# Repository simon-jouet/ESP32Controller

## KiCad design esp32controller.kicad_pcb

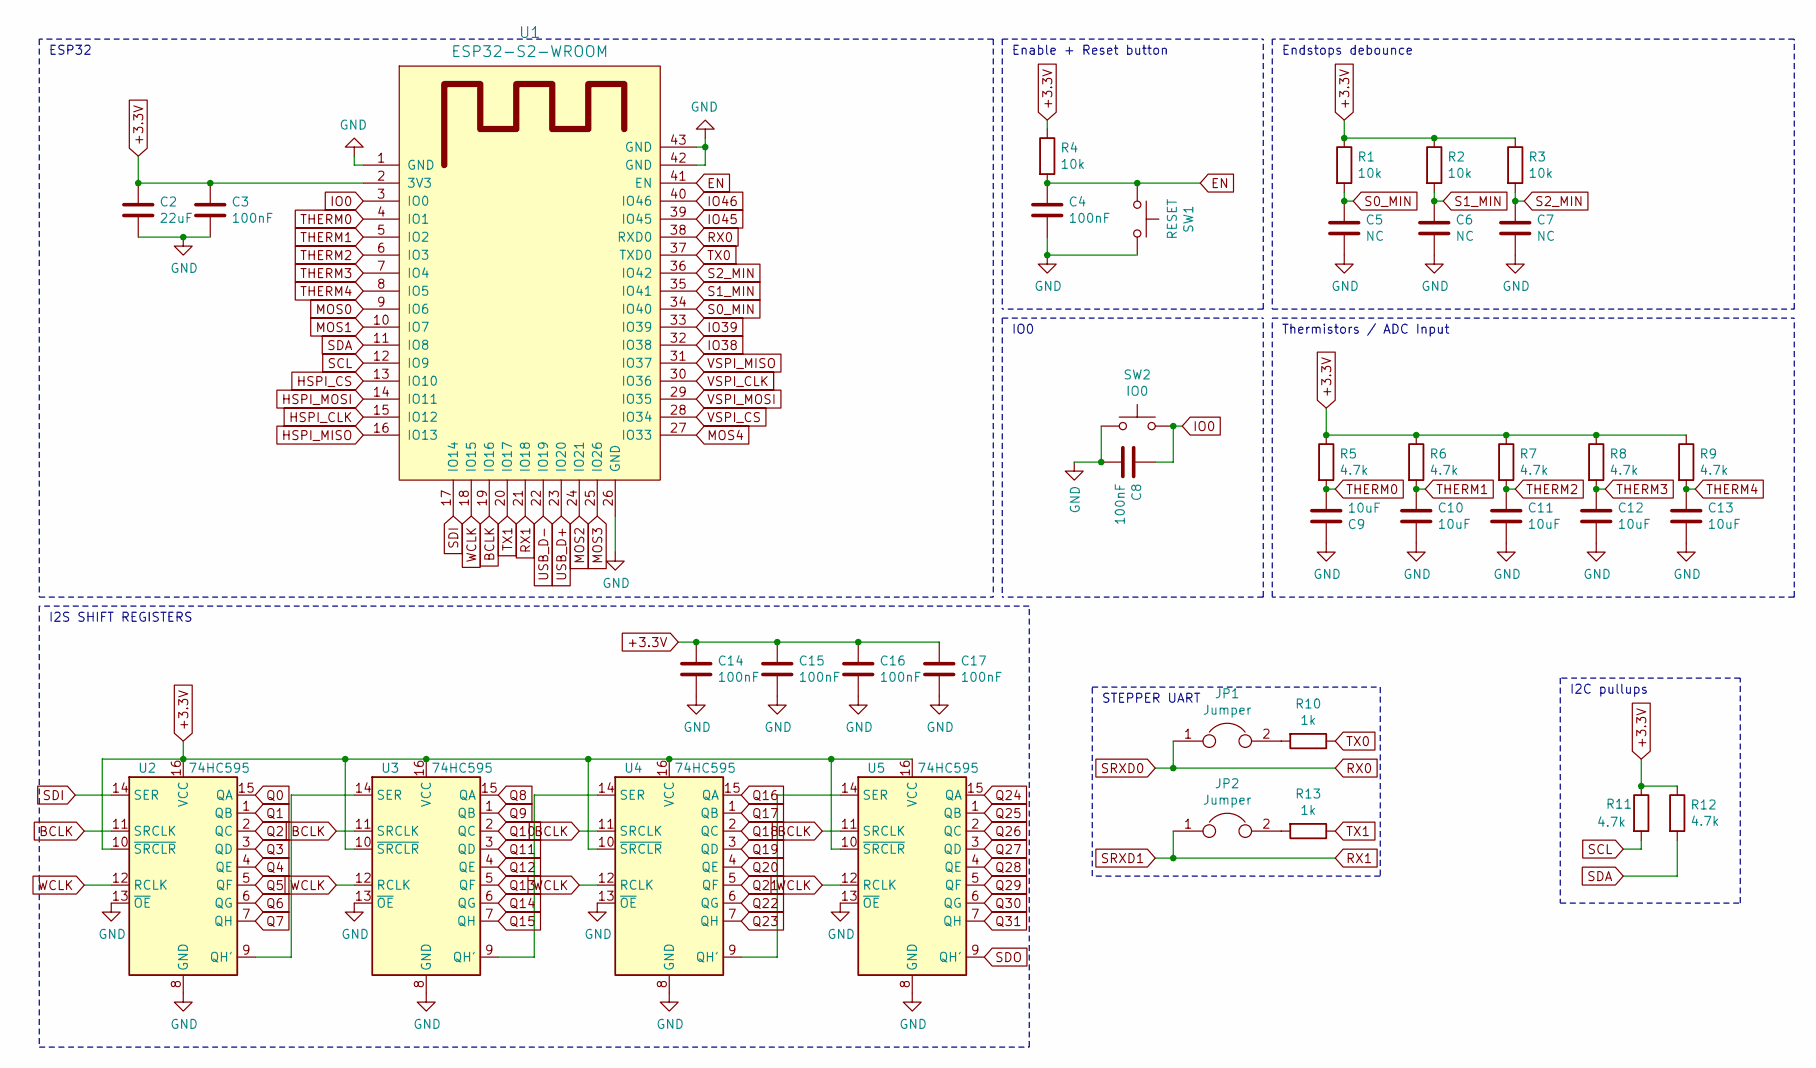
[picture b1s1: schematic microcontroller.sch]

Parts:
C2: 22uF; C_0805_2012Metric
C3, C4, C8, C14, C15, C16, C17: 100nF; C_0603_1608Metric
C5, C6, C7: NC; C_0603_1608Metric
C9, C10, C11, C12, C13: 10uF; C_0805_2012Metric
JP1, JP2: Jumper; PinHeader_1x02_P2.54mm_Vertical
R1, R2, R3, R4: 10k; R_0603_1608Metric
R5, R6, R7, R8, R9, R11, R12: 4.7k; R_0603_1608Metric
R10, R13: 1k; R_0603_1608Metric
SW1: RESET; SW_Push_1P1T_NO_6x6mm_H9.5mm
SW2: IO0; SW_Push_1P1T_NO_6x6mm_H9.5mm
U1: ESP32-S2-WROOM; esp32-s2-wrooom
U2, U3, U4, U5: 74HC595; TSSOP-16_4.4x5mm_P0.65mm

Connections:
+3.3V: C2.1, C3.1, C14.1, C15.1, C16.1, C17.1, R1.1, R2.1, R3.1, R4.1, R5.1, R6.1, R7.1, R8.1, R9.1, R11.1, R12.1, U1.2 (3V3), U2.10 (~SRCLR), U2.16 (VCC), U3.10 (~SRCLR), U3.16 (VCC), U4.10 (~SRCLR), U4.16 (VCC), U5.10 (~SRCLR), U5.16 (VCC); also elsewhere on the board
BCLK: U1.19 (IO16), U2.11 (SRCLK), U3.11 (SRCLK), U4.11 (SRCLK), U5.11 (SRCLK)
EN: C4.1, R4.2, SW1.1, U1.41 (EN); also elsewhere on the board
GND: C2.2, C3.2, C4.2, C5.2, C6.2, C7.2, C8.2, C9.1, C10.2, C11.2, C12.2, C13.2, C14.2, C15.2, C16.2, C17.2, SW1.2, SW2.1, U1.1 (GND), U1.26 (GND), U1.42 (GND), U1.43 (GND), U2.8 (GND), U2.13 (~OE), U3.8 (GND), U3.13 (~OE), U4.8 (GND), U4.13 (~OE), U5.8 (GND), U5.13 (~OE); also elsewhere on the board
HSPI_CLK: U1.15 (IO12); also elsewhere on the board
HSPI_CS: U1.13 (IO10); also elsewhere on the board
HSPI_MISO: U1.16 (IO13); also elsewhere on the board
HSPI_MOSI: U1.14 (IO11); also elsewhere on the board
IO0: C8.1, SW2.2, U1.3 (IO0); also elsewhere on the board
IO38: U1.32 (IO38); also elsewhere on the board
IO39: U1.33 (IO39); also elsewhere on the board
IO45: U1.39 (IO45); also elsewhere on the board
IO46: U1.40 (IO46); also elsewhere on the board
MOS0: U1.9 (IO6); also elsewhere on the board
MOS1: U1.10 (IO7); also elsewhere on the board
MOS2: U1.24 (IO21); also elsewhere on the board
MOS3: U1.25 (IO26); also elsewhere on the board
MOS4: U1.27 (IO33); also elsewhere on the board
unnamed: JP1.2, R10.2
unnamed: JP2.2, R13.2
unnamed: U2.9 (QH'), U3.14 (SER)
unnamed: U3.9 (QH'), U4.14 (SER)
unnamed: U4.9 (QH'), U5.14 (SER)
Q0: U2.15 (QA); also elsewhere on the board
Q1: U2.1 (QB); also elsewhere on the board
Q2: U2.2 (QC); also elsewhere on the board
Q3: U2.3 (QD); also elsewhere on the board
Q4: U2.4 (QE); also elsewhere on the board
Q5: U2.5 (QF); also elsewhere on the board
Q6: U2.6 (QG); also elsewhere on the board
Q7: U2.7 (QH); also elsewhere on the board
Q8: U3.15 (QA); also elsewhere on the board
Q9: U3.1 (QB); also elsewhere on the board
Q10: U3.2 (QC); also elsewhere on the board
Q11: U3.3 (QD); also elsewhere on the board
Q12: U3.4 (QE); also elsewhere on the board
Q13: U3.5 (QF); also elsewhere on the board
Q14: U3.6 (QG); also elsewhere on the board
Q15: U3.7 (QH); also elsewhere on the board
Q16: U4.15 (QA); also elsewhere on the board
Q17: U4.1 (QB); also elsewhere on the board
Q18: U4.2 (QC); also elsewhere on the board
Q19: U4.3 (QD); also elsewhere on the board
Q20: U4.4 (QE); also elsewhere on the board
Q21: U4.5 (QF); also elsewhere on the board
Q22: U4.6 (QG); also elsewhere on the board
Q23: U4.7 (QH); also elsewhere on the board
Q24: U5.15 (QA); also elsewhere on the board
Q25: U5.1 (QB); also elsewhere on the board
Q26: U5.2 (QC); also elsewhere on the board
Q27: U5.3 (QD); also elsewhere on the board
Q28: U5.4 (QE); also elsewhere on the board
Q29: U5.5 (QF); also elsewhere on the board
Q30: U5.6 (QG); also elsewhere on the board
Q31: U5.7 (QH); also elsewhere on the board
RX0: JP1.1, U1.38 (RXD0); also elsewhere on the board
RX1: JP2.1, U1.21 (IO18); also elsewhere on the board
S0_MIN: C5.1, R1.2, U1.34 (IO40); also elsewhere on the board
S1_MIN: C6.1, R2.2, U1.35 (IO41); also elsewhere on the board
S2_MIN: C7.1, R3.2, U1.36 (IO42); also elsewhere on the board
SCL: R11.2, U1.12 (IO9); also elsewhere on the board
SDA: R12.2, U1.11 (IO8); also elsewhere on the board
SDI: U1.17 (IO14), U2.14 (SER)
THERM0: C9.2, R5.2, U1.4 (IO1); also elsewhere on the board
THERM1: C10.1, R6.2, U1.5 (IO2); also elsewhere on the board
THERM2: C11.1, R7.2, U1.6 (IO3); also elsewhere on the board
THERM3: C12.1, R8.2, U1.7 (IO4); also elsewhere on the board
THERM4: C13.1, R9.2, U1.8 (IO5); also elsewhere on the board
TX0: R10.1, U1.37 (TXD0); also elsewhere on the board
TX1: R13.1, U1.20 (IO17); also elsewhere on the board
USB_D+: U1.23 (IO20); also elsewhere on the board
USB_D-: U1.22 (IO19); also elsewhere on the board
VSPI_CLK: U1.30 (IO36); also elsewhere on the board
VSPI_CS: U1.28 (IO34); also elsewhere on the board
VSPI_MISO: U1.31 (IO37); also elsewhere on the board
VSPI_MOSI: U1.29 (IO35); also elsewhere on the board
WCLK: U1.18 (IO15), U2.12 (RCLK), U3.12 (RCLK), U4.12 (RCLK), U5.12 (RCLK)

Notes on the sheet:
ESP32
I2S SHIFT REGISTERS
Endstops debounce
Enable + Reset button
Thermistors / ADC Input
I2C pullups
IO0
STEPPER UART

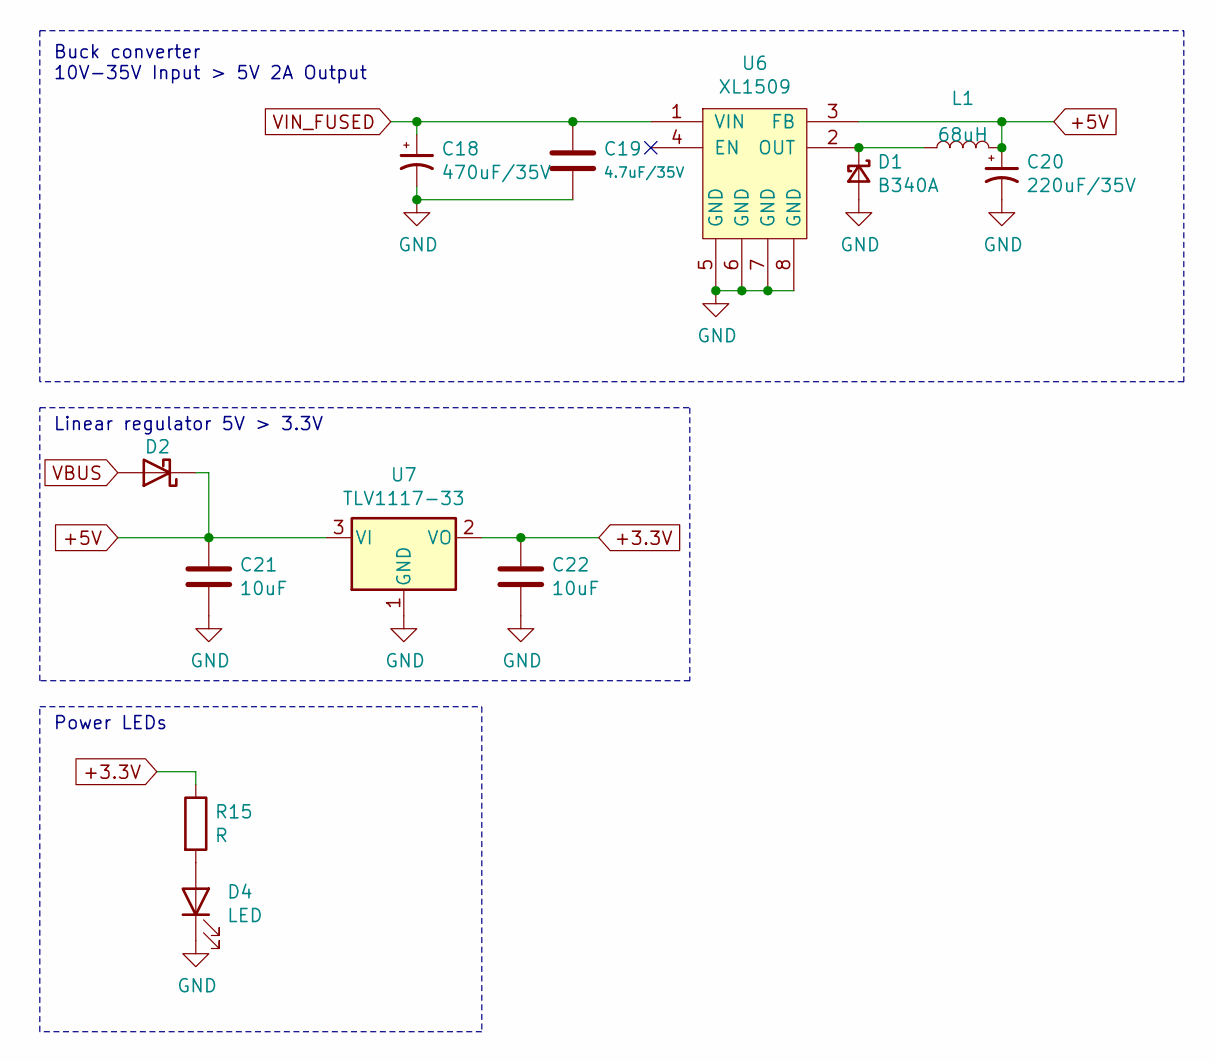
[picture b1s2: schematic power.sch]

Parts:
C18: 470uF/35V; CP_Elec_10x10
C19: 4.7uF/35V; C_0805_2012Metric
C20: 220uF/35V; C_1210_3225Metric
C21, C22: 10uF; C_0805_2012Metric
D1: B340A; D_SMA
D2: D_Schottky; D_SOD-323_HandSoldering
D4: LED; LED_0805_2012Metric
L1: 68uH; L_7.3x7.3_H3.5
R15: R; R_0603_1608Metric
U6: XL1509; SOIC-8_3.9x4.9mm_P1.27mm
U7: TLV1117-33; SOT-223-3_TabPin2

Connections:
+3.3V: C22.1, R15.1, U7.2 (VO); also elsewhere on the board
+5V: C20.1, C21.1, D2.1 (K), L1.2, U6.3 (FB), U7.3 (VI); also elsewhere on the board
GND: C18.2, C19.2, C20.2, C21.2, C22.2, D1.2 (A), D4.1 (K), U6.5 (GND), U6.6 (GND), U6.7 (GND), U6.8 (GND), U7.1 (GND); also elsewhere on the board
unnamed: D1.1 (K), L1.1, U6.2 (OUT)
unnamed: D4.2 (A), R15.2
VBUS: D2.2 (A); also elsewhere on the board
VIN_FUSED: C18.1, C19.1, U6.1 (VIN); also elsewhere on the board

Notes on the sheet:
Linear regulator 5V > 3.3V
Power LEDs
Buck converter 10V-35V Input > 5V 2A Output

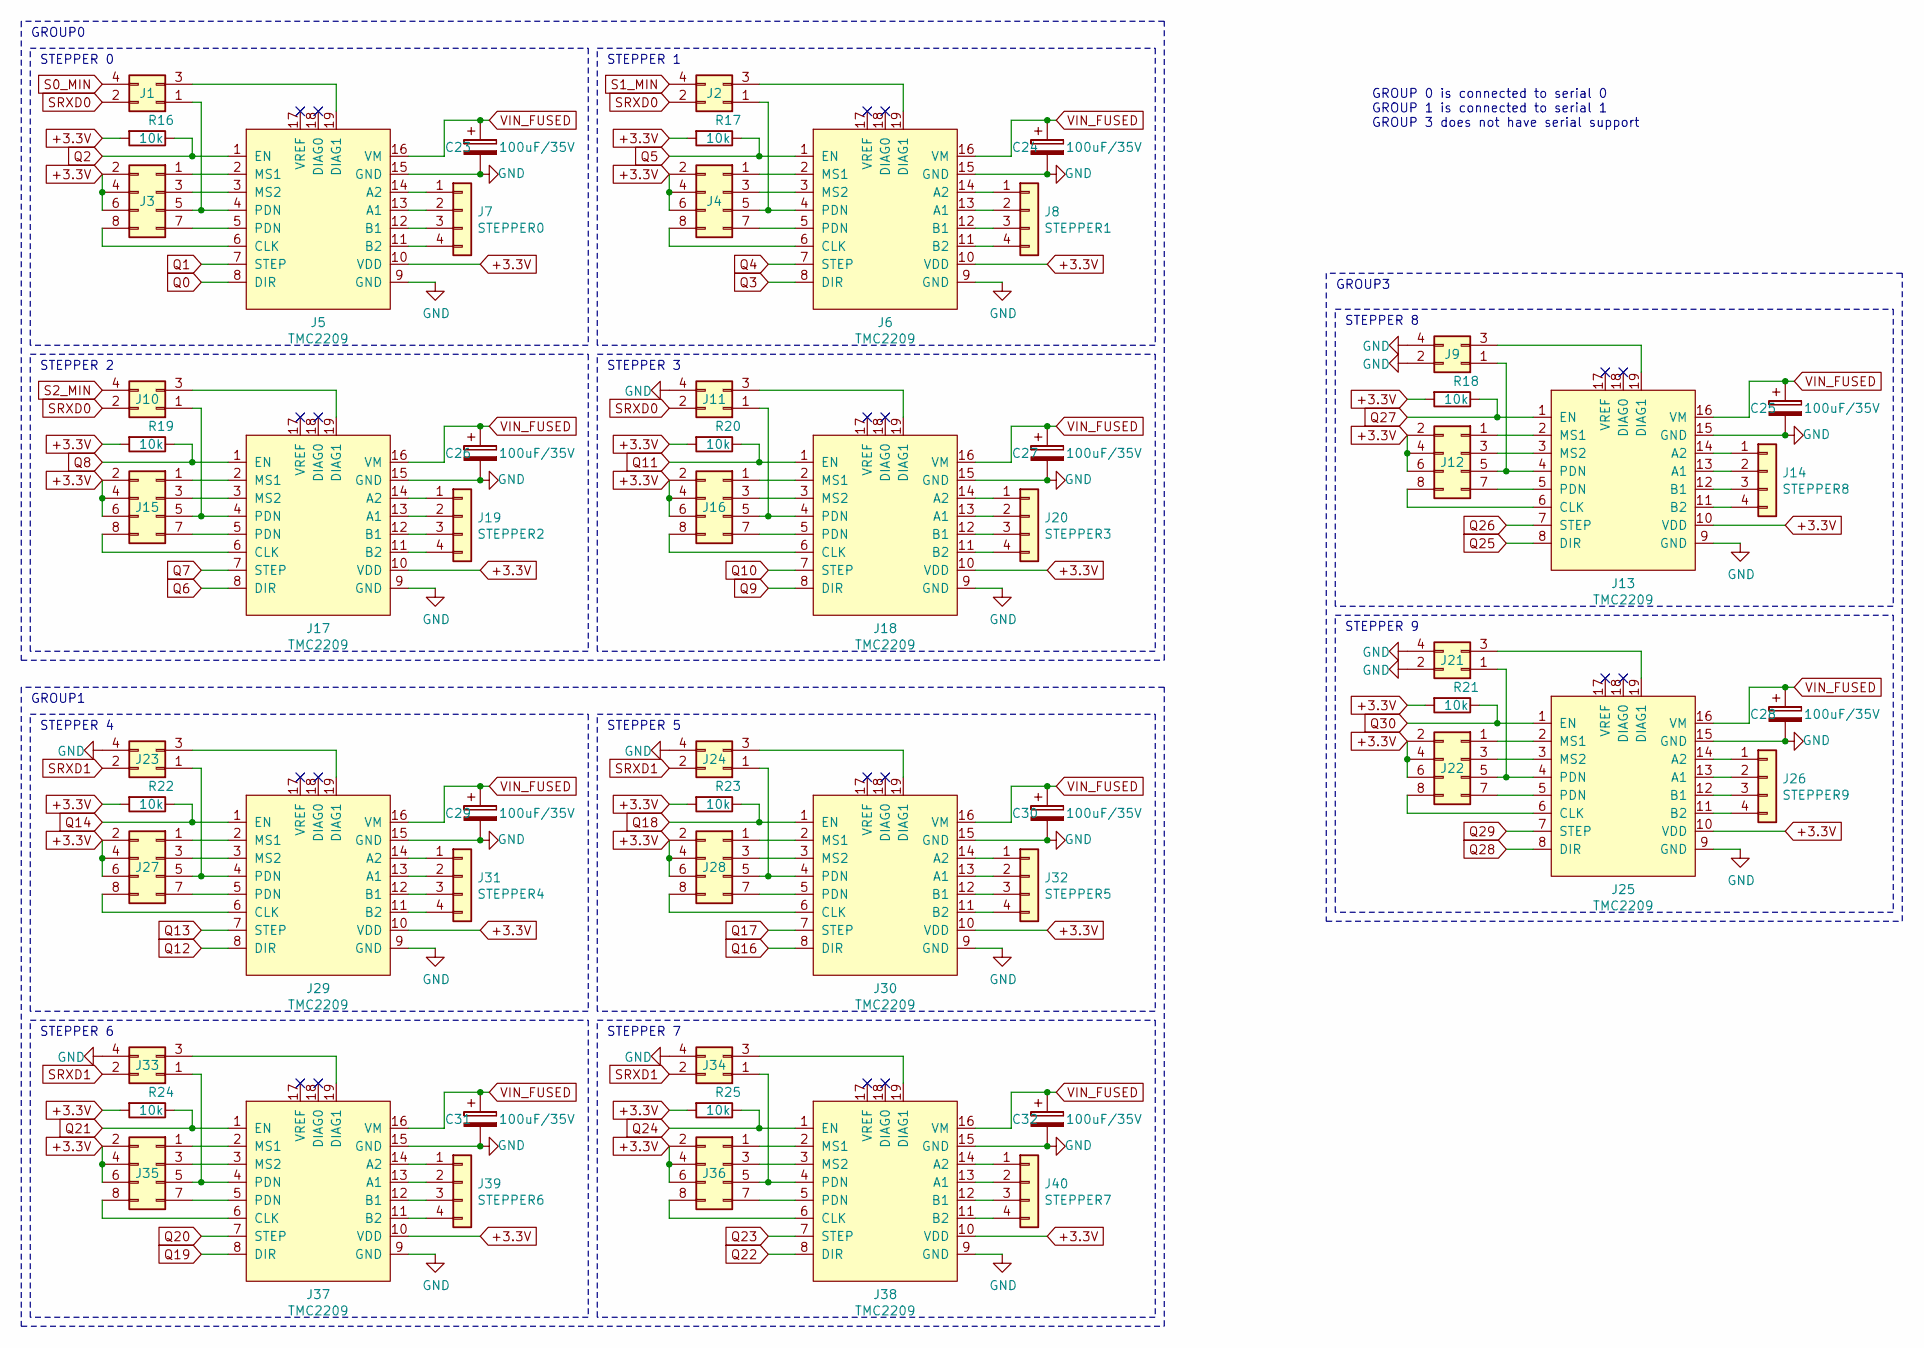
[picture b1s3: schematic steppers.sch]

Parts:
C23, C24, C25, C26, C27, C28, C29, C30, C31, C32: 100uF/35V; CP_Elec_6.3x7.7
J1, J2, J9, J10, J11, J21, J23, J24, J33, J34: Conn_02x02_Odd_Even; PinHeader_1x04_P2.54mm_Vertical
J3, J4, J12, J15, J16, J22, J27, J28, J35, J36: Conn_02x04_Odd_Even; PinHeader_2x04_P2.54mm_Vertical
J5, J6, J13, J17, J18, J25, J29, J30, J37, J38: TMC2209; pololu
J7: STEPPER0; JST_XH_B4B-XH-A_1x04_P2.50mm_Vertical
J8: STEPPER1; JST_XH_B4B-XH-A_1x04_P2.50mm_Vertical
J14: STEPPER8; JST_XH_B4B-XH-A_1x04_P2.50mm_Vertical
J19: STEPPER2; JST_XH_B4B-XH-A_1x04_P2.50mm_Vertical
J20: STEPPER3; JST_XH_B4B-XH-A_1x04_P2.50mm_Vertical
J26: STEPPER9; JST_XH_B4B-XH-A_1x04_P2.50mm_Vertical
J31: STEPPER4; JST_XH_B4B-XH-A_1x04_P2.50mm_Vertical
J32: STEPPER5; JST_XH_B4B-XH-A_1x04_P2.50mm_Vertical
J39: STEPPER6; JST_XH_B4B-XH-A_1x04_P2.50mm_Vertical
J40: STEPPER7; JST_XH_B4B-XH-A_1x04_P2.50mm_Vertical
R16, R17, R18, R19, R20, R21, R22, R23, R24, R25: 10k; R_0603_1608Metric

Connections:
+3.3V: J3.2, J3.4, J3.6, J4.2, J4.4, J4.6, J5.10 (VDD), J6.10 (VDD), J12.2, J12.4, J12.6, J13.10 (VDD), J15.2, J15.4, J15.6, J16.2, J16.4, J16.6, J17.10 (VDD), J18.10 (VDD), J22.2, J22.4, J22.6, J25.10 (VDD), J27.2, J27.4, J27.6, J28.2, J28.4, J28.6, J29.10 (VDD), J30.10 (VDD), J35.2, J35.4, J35.6, J36.2, J36.4, J36.6, J37.10 (VDD), J38.10 (VDD), R16.2, R17.2, R18.2, R19.2, R20.2, R21.2, R22.2, R23.2, R24.2, R25.2; also elsewhere on the board
GND: C23.2, C24.2, C25.2, C26.2, C27.2, C28.2, C29.2, C30.2, C31.2, C32.2, J5.9 (GND), J5.15 (GND), J6.9 (GND), J6.15 (GND), J9.2, J9.4, J11.4, J13.9 (GND), J13.15 (GND), J17.9 (GND), J17.15 (GND), J18.9 (GND), J18.15 (GND), J21.2, J21.4, J23.4, J24.4, J25.9 (GND), J25.15 (GND), J29.9 (GND), J29.15 (GND), J30.9 (GND), J30.15 (GND), J33.4, J34.4, J37.9 (GND), J37.15 (GND), J38.9 (GND), J38.15 (GND); also elsewhere on the board
unnamed: J1.1, J3.5, J5.4 (PDN)
unnamed: J1.3, J5.19 (DIAG1)
unnamed: J2.1, J4.5, J6.4 (PDN)
unnamed: J2.3, J6.19 (DIAG1)
unnamed: J3.1, J5.2 (MS1)
unnamed: J3.3, J5.3 (MS2)
unnamed: J3.7, J5.5 (PDN)
unnamed: J3.8, J5.6 (CLK)
unnamed: J4.1, J6.2 (MS1)
unnamed: J4.3, J6.3 (MS2)
unnamed: J4.7, J6.5 (PDN)
unnamed: J4.8, J6.6 (CLK)
unnamed: J5.11 (B2), J7.4
unnamed: J5.12 (B1), J7.3
unnamed: J5.13 (A1), J7.2
unnamed: J5.14 (A2), J7.1
unnamed: J6.11 (B2), J8.4
unnamed: J6.12 (B1), J8.3
unnamed: J6.13 (A1), J8.2
unnamed: J6.14 (A2), J8.1
unnamed: J10.1, J15.5, J17.4 (PDN)
unnamed: J10.3, J17.19 (DIAG1)
unnamed: J11.1, J16.5, J18.4 (PDN)
unnamed: J11.3, J18.19 (DIAG1)
unnamed: J12.1, J13.2 (MS1)
unnamed: J12.3, J13.3 (MS2)
unnamed: J9.1, J12.5, J13.4 (PDN)
unnamed: J12.7, J13.5 (PDN)
unnamed: J12.8, J13.6 (CLK)
unnamed: J13.11 (B2), J14.4
unnamed: J13.12 (B1), J14.3
unnamed: J13.13 (A1), J14.2
unnamed: J13.14 (A2), J14.1
unnamed: J9.3, J13.19 (DIAG1)
unnamed: J15.1, J17.2 (MS1)
unnamed: J15.3, J17.3 (MS2)
unnamed: J15.7, J17.5 (PDN)
unnamed: J15.8, J17.6 (CLK)
unnamed: J16.1, J18.2 (MS1)
unnamed: J16.3, J18.3 (MS2)
unnamed: J16.7, J18.5 (PDN)
unnamed: J16.8, J18.6 (CLK)
unnamed: J17.11 (B2), J19.4
unnamed: J17.12 (B1), J19.3
unnamed: J17.13 (A1), J19.2
unnamed: J17.14 (A2), J19.1
unnamed: J18.11 (B2), J20.4
unnamed: J18.12 (B1), J20.3
unnamed: J18.13 (A1), J20.2
unnamed: J18.14 (A2), J20.1
unnamed: J21.1, J22.5, J25.4 (PDN)
unnamed: J21.3, J25.19 (DIAG1)
unnamed: J22.1, J25.2 (MS1)
unnamed: J22.3, J25.3 (MS2)
unnamed: J22.7, J25.5 (PDN)
unnamed: J22.8, J25.6 (CLK)
unnamed: J23.1, J27.5, J29.4 (PDN)
unnamed: J23.3, J29.19 (DIAG1)
unnamed: J24.1, J28.5, J30.4 (PDN)
unnamed: J24.3, J30.19 (DIAG1)
unnamed: J25.11 (B2), J26.4
unnamed: J25.12 (B1), J26.3
unnamed: J25.13 (A1), J26.2
unnamed: J25.14 (A2), J26.1
unnamed: J27.1, J29.2 (MS1)
unnamed: J27.3, J29.3 (MS2)
unnamed: J27.7, J29.5 (PDN)
unnamed: J27.8, J29.6 (CLK)
unnamed: J28.1, J30.2 (MS1)
unnamed: J28.3, J30.3 (MS2)
unnamed: J28.7, J30.5 (PDN)
unnamed: J28.8, J30.6 (CLK)
unnamed: J29.11 (B2), J31.4
unnamed: J29.12 (B1), J31.3
unnamed: J29.13 (A1), J31.2
unnamed: J29.14 (A2), J31.1
unnamed: J30.11 (B2), J32.4
unnamed: J30.12 (B1), J32.3
unnamed: J30.13 (A1), J32.2
unnamed: J30.14 (A2), J32.1
unnamed: J33.1, J35.5, J37.4 (PDN)
unnamed: J33.3, J37.19 (DIAG1)
unnamed: J34.1, J36.5, J38.4 (PDN)
unnamed: J34.3, J38.19 (DIAG1)
unnamed: J35.1, J37.2 (MS1)
unnamed: J35.3, J37.3 (MS2)
unnamed: J35.7, J37.5 (PDN)
unnamed: J35.8, J37.6 (CLK)
unnamed: J36.1, J38.2 (MS1)
unnamed: J36.3, J38.3 (MS2)
unnamed: J36.7, J38.5 (PDN)
unnamed: J36.8, J38.6 (CLK)
unnamed: J37.11 (B2), J39.4
unnamed: J37.12 (B1), J39.3
unnamed: J37.13 (A1), J39.2
unnamed: J37.14 (A2), J39.1
unnamed: J38.11 (B2), J40.4
unnamed: J38.12 (B1), J40.3
unnamed: J38.13 (A1), J40.2
unnamed: J38.14 (A2), J40.1
Q0: J5.8 (DIR); also elsewhere on the board
Q1: J5.7 (STEP); also elsewhere on the board
Q2: J5.1 (EN), R16.1; also elsewhere on the board
Q3: J6.8 (DIR); also elsewhere on the board
Q4: J6.7 (STEP); also elsewhere on the board
Q5: J6.1 (EN), R17.1; also elsewhere on the board
Q6: J17.8 (DIR); also elsewhere on the board
Q7: J17.7 (STEP); also elsewhere on the board
Q8: J17.1 (EN), R19.1; also elsewhere on the board
Q9: J18.8 (DIR); also elsewhere on the board
Q10: J18.7 (STEP); also elsewhere on the board
Q11: J18.1 (EN), R20.1; also elsewhere on the board
Q12: J29.8 (DIR); also elsewhere on the board
Q13: J29.7 (STEP); also elsewhere on the board
Q14: J29.1 (EN), R22.1; also elsewhere on the board
Q16: J30.8 (DIR); also elsewhere on the board
Q17: J30.7 (STEP); also elsewhere on the board
Q18: J30.1 (EN), R23.1; also elsewhere on the board
Q19: J37.8 (DIR); also elsewhere on the board
Q20: J37.7 (STEP); also elsewhere on the board
Q21: J37.1 (EN), R24.1; also elsewhere on the board
Q22: J38.8 (DIR); also elsewhere on the board
Q23: J38.7 (STEP); also elsewhere on the board
Q24: J38.1 (EN), R25.1; also elsewhere on the board
Q25: J13.8 (DIR); also elsewhere on the board
Q26: J13.7 (STEP); also elsewhere on the board
Q27: J13.1 (EN), R18.1; also elsewhere on the board
Q28: J25.8 (DIR); also elsewhere on the board
Q29: J25.7 (STEP); also elsewhere on the board
Q30: J25.1 (EN), R21.1; also elsewhere on the board
RX0: J1.2, J2.2, J10.2, J11.2; also elsewhere on the board
RX1: J23.2, J24.2, J33.2, J34.2; also elsewhere on the board
S0_MIN: J1.4; also elsewhere on the board
S1_MIN: J2.4; also elsewhere on the board
S2_MIN: J10.4; also elsewhere on the board
VIN_FUSED: C23.1, C24.1, C25.1, C26.1, C27.1, C28.1, C29.1, C30.1, C31.1, C32.1, J5.16 (VM), J6.16 (VM), J13.16 (VM), J17.16 (VM), J18.16 (VM), J25.16 (VM), J29.16 (VM), J30.16 (VM), J37.16 (VM), J38.16 (VM); also elsewhere on the board

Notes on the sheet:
STEPPER 0
STEPPER 1
STEPPER 8
STEPPER 2
STEPPER 3
STEPPER 9
STEPPER 4
STEPPER 5
STEPPER 6
STEPPER 7
GROUP0
GROUP1
GROUP 0 is connected to serial 0 GROUP 1 is connected to serial 1 GROUP 3 does not have serial support
GROUP3

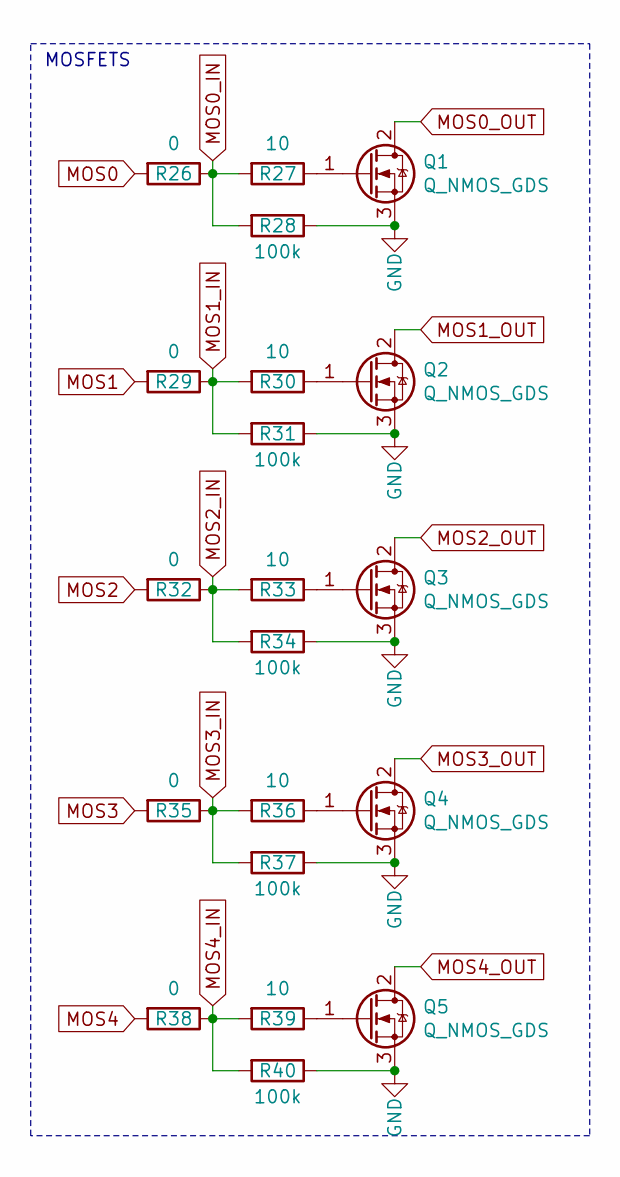
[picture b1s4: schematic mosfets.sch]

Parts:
Q1, Q2, Q3, Q4, Q5: Q_NMOS_GDS; TO-252-2
R26, R29, R32, R35, R38: 0; R_0603_1608Metric
R27, R30, R33, R36, R39: 10; R_0603_1608Metric
R28, R31, R34, R37, R40: 100k; R_0603_1608Metric

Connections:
GND: Q1.3 (S), Q2.3 (S), Q3.3 (S), Q4.3 (S), Q5.3 (S), R28.1, R31.1, R34.1, R37.1, R40.1; also elsewhere on the board
MOS0: R26.2; also elsewhere on the board
MOS0_IN: R26.1, R27.2, R28.2
MOS0_OUT: Q1.2 (D); also elsewhere on the board
MOS1: R29.2; also elsewhere on the board
MOS1_IN: R29.1, R30.2, R31.2
MOS1_OUT: Q2.2 (D); also elsewhere on the board
MOS2: R32.2; also elsewhere on the board
MOS2_IN: R32.1, R33.2, R34.2
MOS2_OUT: Q3.2 (D); also elsewhere on the board
MOS3: R35.2; also elsewhere on the board
MOS3_IN: R35.1, R36.2, R37.2
MOS3_OUT: Q4.2 (D); also elsewhere on the board
MOS4: R38.2; also elsewhere on the board
MOS4_IN: R38.1, R39.2, R40.2
MOS4_OUT: Q5.2 (D); also elsewhere on the board
unnamed: Q1.1 (G), R27.1
unnamed: Q2.1 (G), R30.1
unnamed: Q3.1 (G), R33.1
unnamed: Q4.1 (G), R36.1
unnamed: Q5.1 (G), R39.1

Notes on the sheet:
MOSFETS

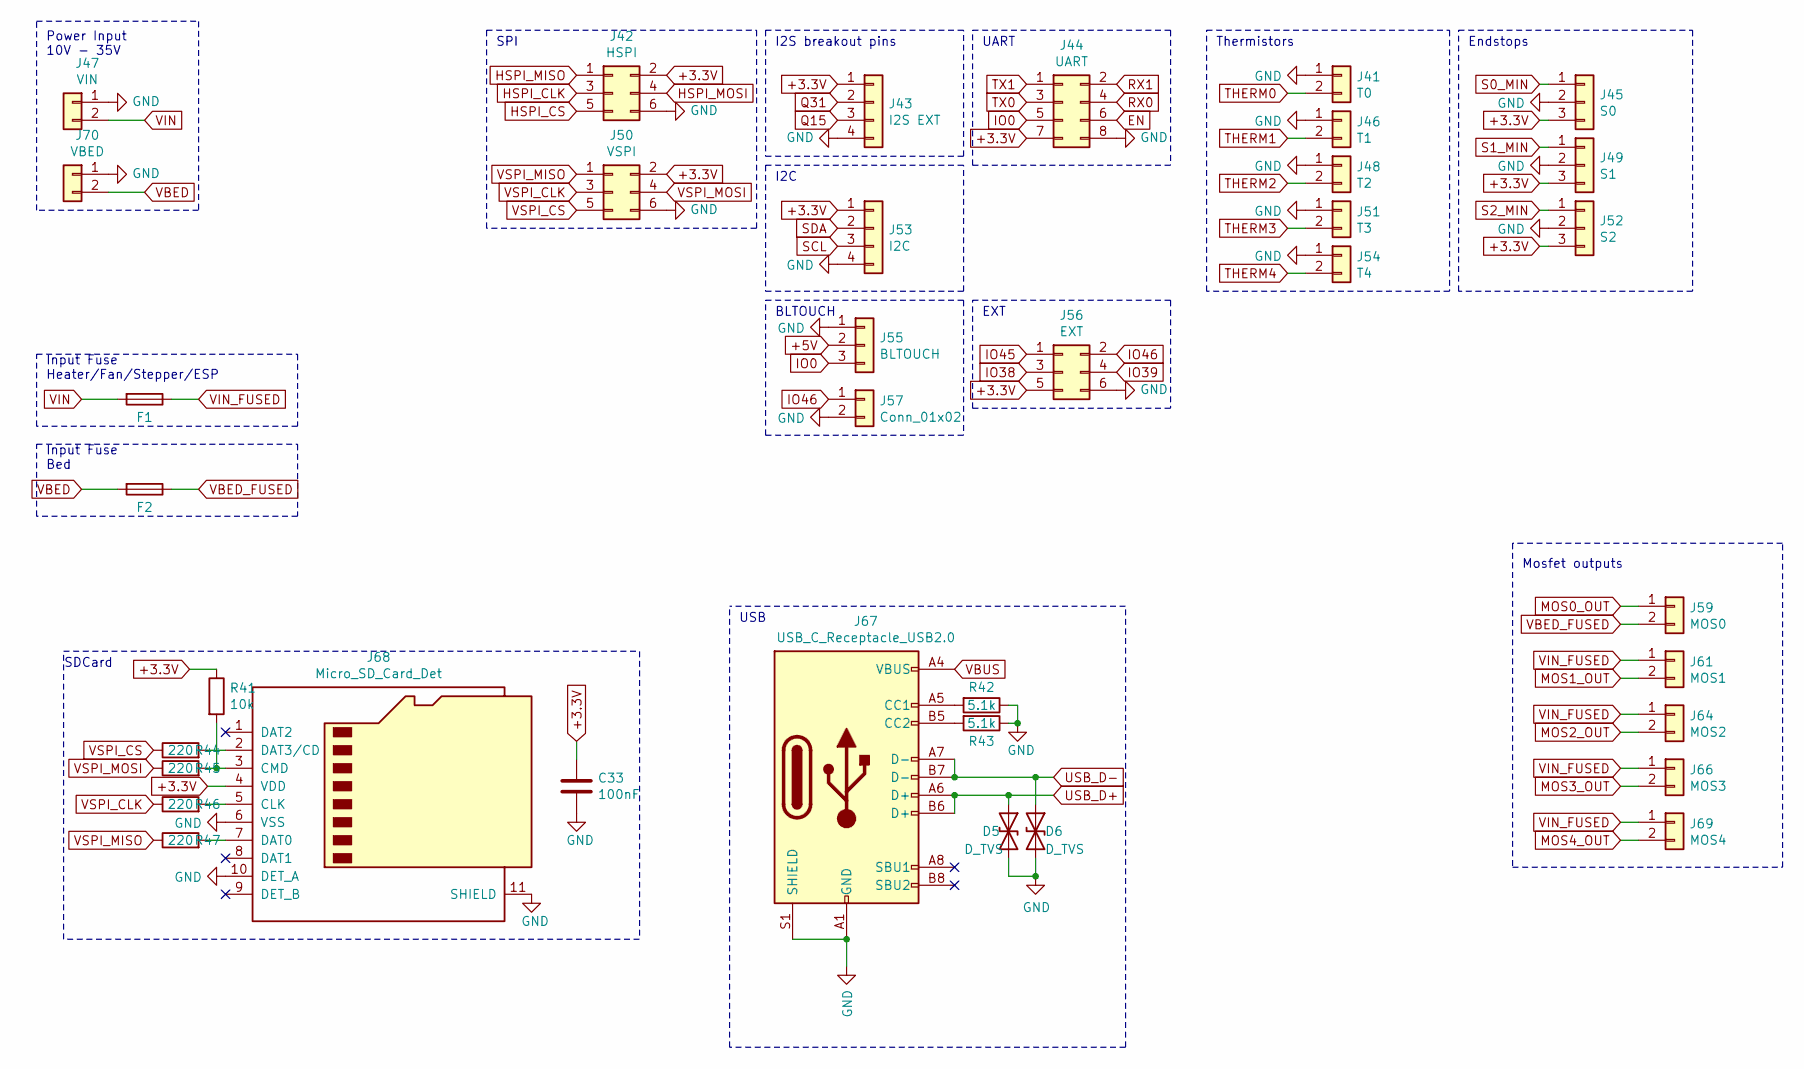
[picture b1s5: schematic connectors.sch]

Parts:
C33: 100nF; C_0603_1608Metric
D5, D6: D_TVS; D_SOD-523
F1, F2: Fuse; Fuse_holder_0679H
J41: T0; JST_XH_B2B-XH-A_1x02_P2.50mm_Vertical
J42: HSPI; IDC-Header_2x03_P2.54mm_Vertical
J43: I2S EXT; JST_XH_B4B-XH-A_1x04_P2.50mm_Vertical
J44: UART; IDC-Header_2x04_P2.54mm_Vertical
J45: S0; JST_XH_B3B-XH-A_1x03_P2.50mm_Vertical
J46: T1; JST_XH_B2B-XH-A_1x02_P2.50mm_Vertical
J47: VIN; TERM_2-WAY_6.35mm
J48: T2; JST_XH_B2B-XH-A_1x02_P2.50mm_Vertical
J49: S1; JST_XH_B3B-XH-A_1x03_P2.50mm_Vertical
J50: VSPI; IDC-Header_2x03_P2.54mm_Vertical
J51: T3; JST_XH_B2B-XH-A_1x02_P2.50mm_Vertical
J52: S2; JST_XH_B3B-XH-A_1x03_P2.50mm_Vertical
J53: I2C; JST_XH_B4B-XH-A_1x04_P2.50mm_Vertical
J54: T4; JST_XH_B2B-XH-A_1x02_P2.50mm_Vertical
J55: BLTOUCH; PinHeader_1x03_P2.54mm_Vertical
J56: EXT; IDC-Header_2x03_P2.54mm_Vertical
J57: Conn_01x02; PinHeader_1x02_P2.54mm_Vertical
J59: MOS0; TERM_2-WAY_6.35mm
J61: MOS1; TerminalBlock_bornier-2_P5.08mm
J64: MOS2; TerminalBlock_bornier-2_P5.08mm
J66: MOS3; TerminalBlock_bornier-2_P5.08mm
J67: USB_C_Receptacle_USB2.0; USB_C
J68: Micro_SD_Card_Det; microsd
J69: MOS4; TerminalBlock_bornier-2_P5.08mm
J70: VBED; TERM_2-WAY_6.35mm
R41: 10k; R_0603_1608Metric
R42, R43: 5.1k; R_0603_1608Metric
R44, R45, R46, R47: 220; R_0603_1608Metric

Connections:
+3.3V: C33.1, J42.2, J43.1, J44.7, J45.3, J49.3, J50.2, J52.3, J53.1, J56.5, J68.4 (VDD), R41.1; also elsewhere on the board
+5V: J55.2; also elsewhere on the board
EN: J44.6; also elsewhere on the board
GND: C33.2, D5.2 (A2), D6.2 (A2), J41.1, J42.6, J43.4, J44.8, J45.2, J46.1, J47.1, J48.1, J49.2, J50.6, J51.1, J52.2, J53.4, J54.1, J55.1, J56.6, J57.2, J67.A1 (GND), J67.A12 (GND), J67.B1 (GND), J67.B12 (GND), J67.S1 (SHIELD), J68.6 (VSS), J68.10 (DET_A), J68.11 (SHIELD), J70.1, R42.1, R43.1; also elsewhere on the board
HSPI_CLK: J42.3; also elsewhere on the board
HSPI_CS: J42.5; also elsewhere on the board
HSPI_MISO: J42.1; also elsewhere on the board
HSPI_MOSI: J42.4; also elsewhere on the board
IO0: J44.5, J55.3; also elsewhere on the board
IO38: J56.3; also elsewhere on the board
IO39: J56.4; also elsewhere on the board
IO45: J56.1; also elsewhere on the board
IO46: J56.2, J57.1; also elsewhere on the board
MOS0_OUT: J59.1; also elsewhere on the board
MOS1_OUT: J61.2; also elsewhere on the board
MOS2_OUT: J64.2; also elsewhere on the board
MOS3_OUT: J66.2; also elsewhere on the board
MOS4_OUT: J69.2; also elsewhere on the board
unnamed: J67.A5 (CC1), R42.2
unnamed: J67.B5 (CC2), R43.2
unnamed: J68.2 (DAT3/CD), R44.2
unnamed: J68.3 (CMD), R41.2, R45.2
unnamed: J68.5 (CLK), R46.2
unnamed: J68.7 (DAT0), R47.2
Q15: J43.3; also elsewhere on the board
Q31: J43.2; also elsewhere on the board
RX0: J44.4; also elsewhere on the board
RX1: J44.2; also elsewhere on the board
S0_MIN: J45.1; also elsewhere on the board
S1_MIN: J49.1; also elsewhere on the board
S2_MIN: J52.1; also elsewhere on the board
SCL: J53.3; also elsewhere on the board
SDA: J53.2; also elsewhere on the board
THERM0: J41.2; also elsewhere on the board
THERM1: J46.2; also elsewhere on the board
THERM2: J48.2; also elsewhere on the board
THERM3: J51.2; also elsewhere on the board
THERM4: J54.2; also elsewhere on the board
TX0: J44.3; also elsewhere on the board
TX1: J44.1; also elsewhere on the board
USB_D+: D5.1 (A1), J67.A6 (D+), J67.B6 (D+); also elsewhere on the board
USB_D-: D6.1 (A1), J67.A7 (D-), J67.B7 (D-); also elsewhere on the board
VBED: F2.2, J70.2
VBED_FUSED: F2.1, J59.2
VBUS: J67.A4 (VBUS), J67.A9 (VBUS), J67.B4 (VBUS), J67.B9 (VBUS); also elsewhere on the board
VIN: F1.2, J47.2
VIN_FUSED: F1.1, J61.1, J64.1, J66.1, J69.1; also elsewhere on the board
VSPI_CLK: J50.3, R46.1; also elsewhere on the board
VSPI_CS: J50.5, R44.1; also elsewhere on the board
VSPI_MISO: J50.1, R47.1; also elsewhere on the board
VSPI_MOSI: J50.4, R45.1; also elsewhere on the board

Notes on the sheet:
Endstops
Power Input 10V - 35V
Input Fuse Heater/Fan/Stepper/ESP
Input Fuse Bed
I2S breakout pins
Mosfet outputs
Thermistors
SDCard
USB
SPI
I2C
UART
BLTOUCH
EXT

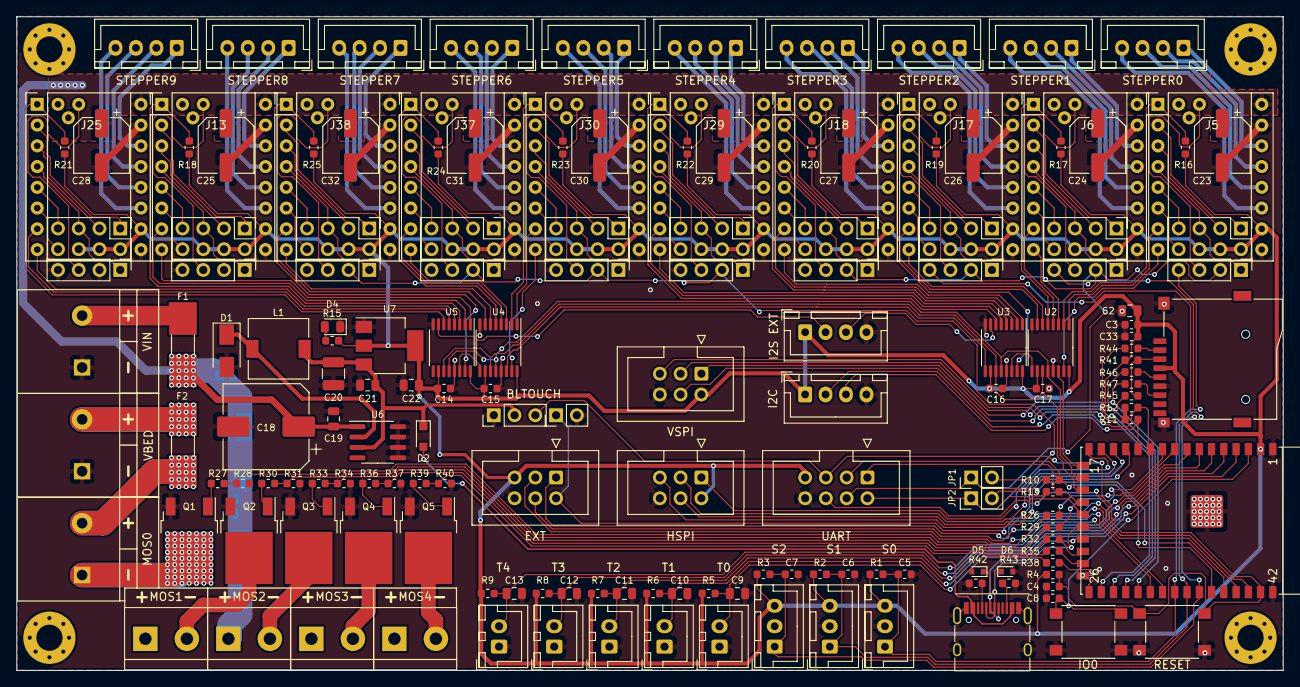
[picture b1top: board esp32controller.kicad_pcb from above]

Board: 2 copper layers, 155.0 x 80.0 mm, 167 parts (0 on the bottom side), 206 nets.

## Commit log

2018-07-05 Prototype R1
2019-04-13 revision 2 with i2s schematic
2019-06-02 improve schematic, fix footprints
2019-06-02 Fix micro SD footprint
2019-06-10 Fixed Therm2 connection, mirrored Jumper for routability
2019-06-10 Routed PCB
2019-06-10 Fixed overlapping Fill Zones
2019-06-23 tweaks
    - use more consistent resitor values
    - DNP R10, parallel with R21
    - fix therm2 connection
2019-06-23 added test points
2019-06-23 use loop footprint for testpoints
2019-06-29 split schematic, update power circuit, switch to usb type c
2019-06-30 start R2 PCB
2019-07-04 finish routing
2019-07-05 small tweaks
2019-07-05 gerber files
2021-06-30 Prototype R3
2021-07-01 Prototype R2
2021-07-06 add readme and images
